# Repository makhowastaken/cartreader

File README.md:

# cartreader (name pending)

Apologies in advance, this repo is really all over the place. I'm trying to organize and document as I go and it's honestly taken more work to clean this project up and organize it than it has to actually create it in the first place. Things *will* be renamed eventually. 

This device was created from the schematic of [sanni's cart reader](https://github.com/sanni/cartreader) and even uses the same, unmodified firmware. Please see that repo for firmware and firmware updates. This device consists of two parts, the control unit which features the arduino itself, the peripherals, and the power supply, and then the interface adapter, which is largely just a passive adapter to allow you to insert whatever cart. Currently, feature parity has not been reached as I have yet to implement a N64 or Megadrive/Genesis adapter. 

## control unit ("sanni_pro")

The Brians of the device. This uses the aftermarket ATMEGA2560 "Pro" boards for a smaller footprint. The actual hardware is largely unchanged from the original Arduino Pros but the footprint is massively reduced. 

This part is designed to be "self contained" and will include all the hardware necessary to operate the device in a portable manner. You need one or more of the following adapters still. 

[Click here for more info, PCB files, and assembly instructions/information of the control unit.](PCB%20Files/control%20unit)

## gb/c and gba adapter ("sanni_gba")

This is the primary adapter that I made this whole module for. I really liked my original reader but I wanted something smaller. This module may actually be combined with any of the other modules by sandwiching the other module inbetween this board and the control unit module.  

[Click here for more info, PCB files, and assembly instructions/information of the GBA adapter.](PCB%20Files/adapters/sanni_gba_shield)

## 8 bit flash module adapter adapter ("sanni_flash")

This is equivalent to the module that plugs into the SNES/SFC slot on sanni's reader that allows you to directly interface with flash chips. It is working (finally) and should interface with the same modules as sanni's version. Only the TSOP48 adapter is tested and confirmed working. I don't have flash chips to test the other adapters. 

[Click here for more info, PCB files, and assembly instructions/information of the flash adapter.](PCB%20Files/adapters/sanni_flash_shield)

## snes / sfc adapter ("sanni_snes")

This adapter is a work in progress. I have uploaded the current version that I have tested and confirmed works (except for the untested CIC lock circuit but it should be fine). Confirmed dumping of SFC games and functionality with sanni's addon modules that interface with the SNES/SFC slot. 

[Click here for more info, PCB files, and assembly instructions/information of the SFC adapter.](PCB%20Files/adapters/sanni_snes_shield)

## n64 adapter

todo

## md/genesis adapter

todo

## other adapters

Sanni's NES/FC adapters, Wonderswan adapter, and SMS adapter should all work through the SNES/SFC adapter but are currently untested.

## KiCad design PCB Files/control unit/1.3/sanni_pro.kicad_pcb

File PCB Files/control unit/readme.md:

# control unit

Version 1.2c renders

BOM: 

|Part Desc|Link|Alternative Link|Cost (I used)|Notes|
:--|:--|:--|--:|:--|
|Arduino Mega 2560 Pro (EMBED, NOT MINI)|[https://www.aliexpress.com/item/MEGA-2560-PRO-Embed-CH340G-ATMEGA2560-16AU-Chip-With-Male-Pinheaders-Compatible-for-Arduino-Mega2560-Module/32968779271.html](https://www.aliexpress.com/item/MEGA-2560-PRO-Embed-CH340G-ATMEGA2560-16AU-Chip-With-Male-Pinheaders-Compatible-for-Arduino-Mega2560-Module/32968779271.html)|[https://www.aliexpress.com/item/Mega-2560-PRO-Embed-CH340G-ATmega2560-16AU-with-male-pinheaders-Compatible-for-Arduino-Mega-2560/32801785024.html](https://www.aliexpress.com/item/Mega-2560-PRO-Embed-CH340G-ATmega2560-16AU-with-male-pinheaders-Compatible-for-Arduino-Mega-2560/32801785024.html)|$8.60|I’d recommend the RobotDyn version. I’ve purchased four of these modules so far and two RobotDyn units were fine, one off-brand unit was fine while the other was DOA.|
|2x10K 0805 SMT Resistors|https://www.aliexpress.com/item/100Pcs-0805-SMD-1-4W-0R-10M-chip-resistor-0-10R-100R-220R-330R-470R-1K/32858225842.html| |$0.59|Might as well keep these things handy, they are useful for a lot of DIY type things. The board supports through-hole type resistors as well but I’d recommend the surface-mount ones anyway.|
|2x 4.3mm SMT SPST Push Button (OR mech keyboard switch)|https://novelkeys.xyz/collections/switches/products/novelkeys-x-kailh-low-profile-choc-thick-clicks|[https://www.aliexpress.com/item/2024658734.html](https://www.aliexpress.com/item/2024658734.html)|$2.55|I opted for mech keys that I already had on hand. The board supports Cherry MX (or equivalent), Alps (or equivalent), or Kailh Choc. You can also use 6x6 buttons but you’ll have to fold the legs under the button and solder from the side. Additionally, if you use standard tact switches, you want to make sure that the buttons you use stick out a few MM since it’s a bit of a pain in the rear to use them otherwise.|
|2x THT SPDT Slide Switch|https://www.aliexpress.com/item/50PCS-YT1998Y-SK12D07-Toggle-Switch-3Pin-PCB-2-Position-1P2T-SPDT-Miniature-Slide-Switch-Side-Knob/32827322833.html| |$1.75|You only need two of the 50, but I can’t find any smaller quantities for less. If you’ve already built one of Sanni’s cart reader shields, you probably already have these.|
|RGB LED (Common Anode)|[https://www.aliexpress.com/item/20Pcs-Multicolor-4pin-5mm-RGB-Led-Diode-Light-Lamp-Tricolor-Round-Common-Anode-LED-F5-Light/32852334348.html](https://www.aliexpress.com/item/20Pcs-Multicolor-4pin-5mm-RGB-Led-Diode-Light-Lamp-Tricolor-Round-Common-Anode-LED-F5-Light/32852334348.html)|https://www.ebay.com/itm/291548934125|$0.88|You only need one of the 50. Enjoy finding uses for the other 49. You can also omit this entirely.|
|OLED Screen|[https://www.aliexpress.com/item/0-96-inch-IIC-Serial-White-OLED-Display-Module-128X64-I2C-SSD1306-12864-LCD-Screen-Board/32896971385.html](https://www.aliexpress.com/item/0-96-inch-IIC-Serial-White-OLED-Display-Module-128X64-I2C-SSD1306-12864-LCD-Screen-Board/32896971385.html)| |$2.25|Comes in blue or white. Take your pick. I like the white.|
|TP4056 Charge Module with Low Voltage Protection|https://www.aliexpress.com/item/Free-Shipping-5V-1A-Micro-USB-18650-Lithium-Battery-Charging-Board-Charger-Module-Protection-Dual/32453058256.html| |$0.85|Micro USB variant is cheaper but this is your charge port and you can use Mini USB or USB C if you like. As long as you get the protected version, the footprint should match.|
|702540 Cell|[https://www.aliexpress.com/item/32878325857.html](https://www.aliexpress.com/item/32878325857.html)| |$8.00|Any “Game Boy Micro” sized battery should fit perfectly within the space between the actual cart interface shield and the arduino. If you have something laying around, that’s even better as this is the second most expensive part of the build (well, third depending on the PCBs)|
|5v 0.45A Voltage Regulator|[https://www.aliexpress.com/item/32786144773.html](https://www.aliexpress.com/item/32786144773.html)| |$1.54|A regulator that can handle more current would be better but this one is well within spec for Game Boy Games. SNES will require supplementary hardware. Any other three pin regulator should work, just mind that the PCB is expecting the middle pin to be ground.|
|3.3v 0.59A Voltage Regulator|[https://www.aliexpress.com/item/32914681832.html](https://www.aliexpress.com/item/32914681832.html)| |$1.47|Any three pin regulator should work, just mind that the middle pin is ground|
|Micro SD Module|[https://www.aliexpress.com/item/1PCS-Micro-SD-Storage-Expansion-Board-Mciro-SD-TF-Card-Memory-Shield-Module-SPI-For-Arduino/32523546123.html](https://www.aliexpress.com/item/1PCS-Micro-SD-Storage-Expansion-Board-Mciro-SD-TF-Card-Memory-Shield-Module-SPI-For-Arduino/32523546123.html)| |$1.04|This hardware does not support the full size SD Module (but only because I did not include the pins -- electrically, it should work fine).|
|Battery gauge (volt meter panel)|[https://www.aliexpress.com/item/32851937196.html](https://www.aliexpress.com/item/32851937196.html)| |$0.85|This is completely optional, but I like it. I also designed the PCB with this in mind so there will be an empty spot if you omit it.|
||||||
|2.54 MM Headers||||You only need the sockets if you think you might want to take this apart at some point. The sockets are required if you want to do more than rip whatever shield you assemble this with. XL pins are recommended for socket-less builds (not tested or linked).|
| Pins|https://www.aliexpress.com/item/10PCS-40Pin-1x40P-Male-Breakable-Pin-Header-Strip-2-54mm-Long-Blue-Red-White-Green-Yellow/32863408765.html| |$0.55|I had a ton of these laying around. With the pins, you can just break off however many you need and solder those on. You can also double-stack them pretty easily for things like the Arduino. The Arduino probably already came with pins though.|
| Sockets|[https://www.aliexpress.com/item/32889916876.html](https://www.aliexpress.com/item/32889916876.html)| |$4.32|You’ll need to get the 2x3, 2x16, and 2x20 option to socket the Arduino. I do not recommend socketing any other components on this model.|
|Total|||$36.79|Prices may have changed on somethings or shipping may be more or less expensive to your area.|

Please let me know if any parts go out of stock or if the listing disappears so that I can add an alternative. 

Assembly must be completed in order. Due to the close proximity of the parts, flush cutters are required and kapton tape for insulation is *highly* recommended. [Please see my video for an example of assembly.](https://youtu.be/GbIMFZ5j5U0)

---

New v1.3???

I have updated the PCB to use [my soft latching power button circuit](https://github.com/makhowastaken/Soft-Latching-Power-Button) and have otherwise slightly tweaked the traces to look better using oshpark's after dark fab process. Like previous boards, this is functionally identical and the only new feature is a momentary push button (swap one of the SPDT switches for the BOM listed in the above linked repo). Going forward, this is likely the board I will be updating but since I have not changed any critical dimensions, not much should change. 

This revision should work since all I did was combine two tested, working designs but since I have yet to actually assemble one, it should be considered untested.

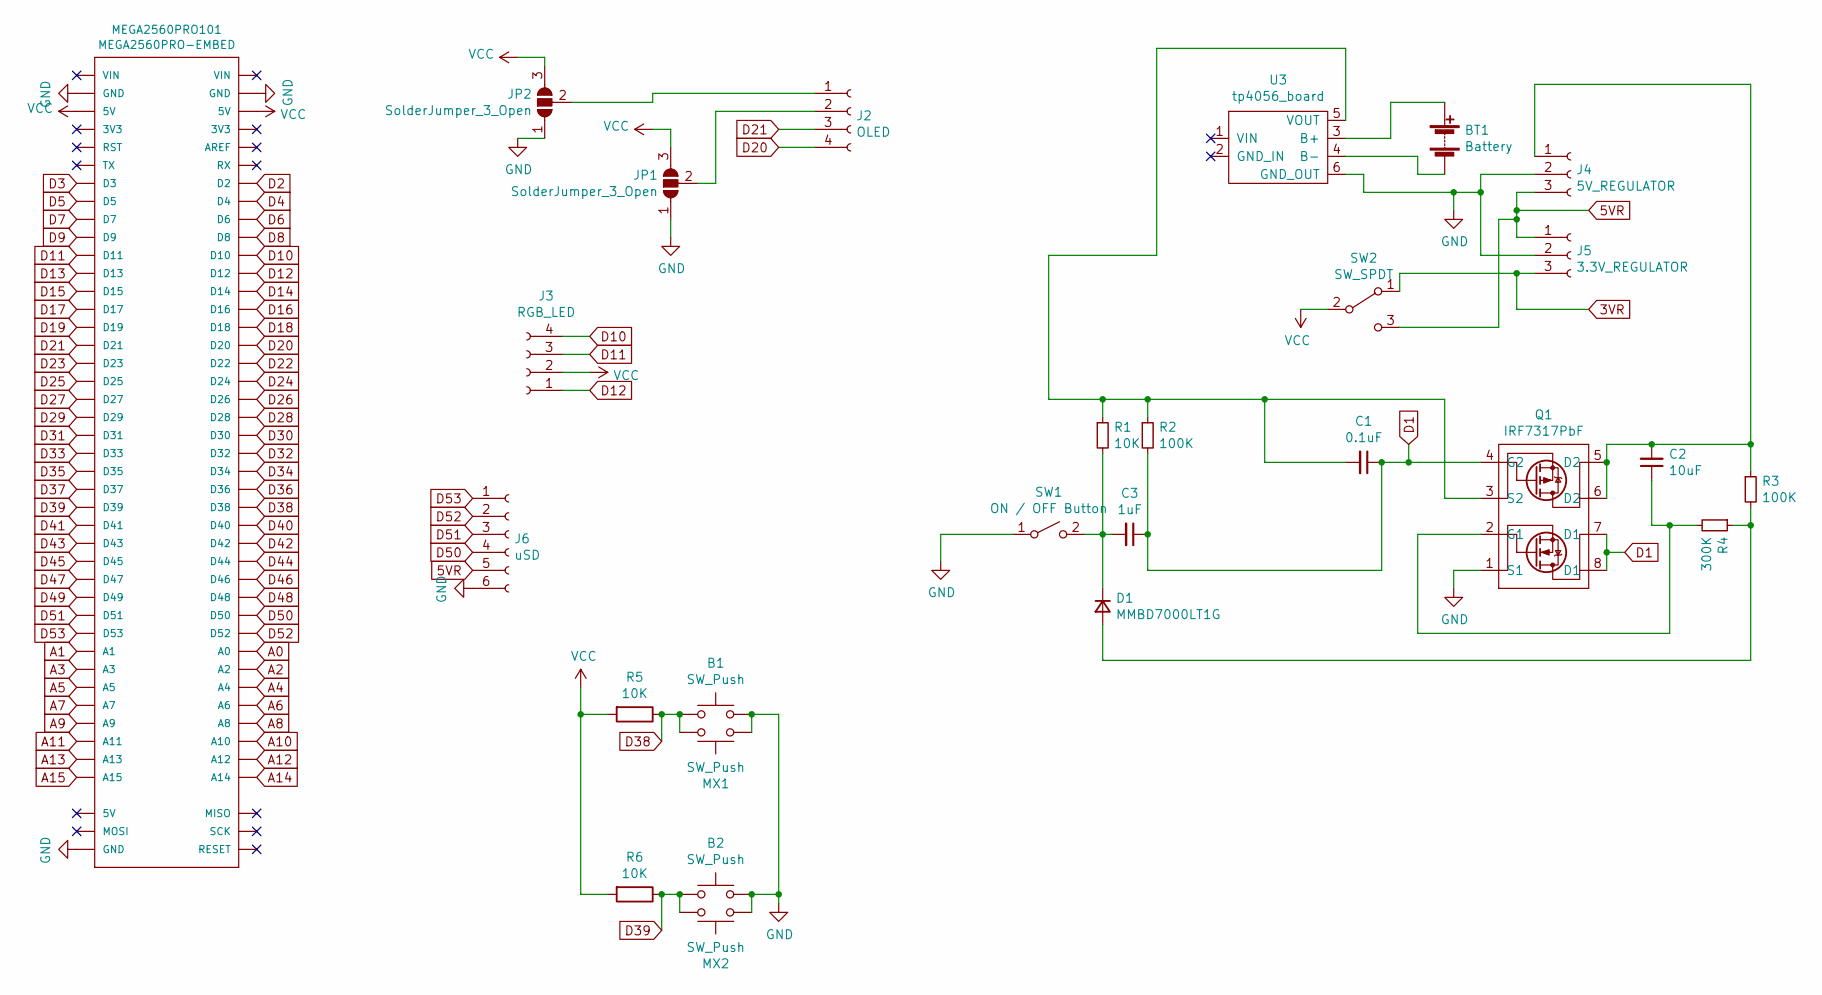
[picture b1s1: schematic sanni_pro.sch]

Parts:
B1, B2: SW_Push; SW_SPST_TL3342
BT1: Battery; PinHeader_1x02_P2.54mm_Vertical
C1: 0.1uF; C_0603_1608Metric_Pad1.05x0.95mm_HandSolder
C2: 10uF; C_0603_1608Metric_Pad1.05x0.95mm_HandSolder
C3: 1uF; C_0603_1608Metric_Pad1.05x0.95mm_HandSolder
D1: MMBD7000LT1G; D_SOT-23_ANK
J2: OLED; OLED_Module
J3: RGB_LED; PinSocket_1x04_P2.54mm_Vertical
J4: 5V_REGULATOR; PinSocket_1x03_P2.54mm_Vertical
J5: 3.3V_REGULATOR; PinSocket_1x03_P2.54mm_Vertical
J6: uSD; Catalex_uSD_BSilk
JP1, JP2: SolderJumper_3_Open; SolderJumper-3_P1.3mm_Open_RoundedPad1.0x1.5mm
MEGA2560PRO101: MEGA2560PRO-EMBED
MX1, MX2: SW_Push; MX-Alps-Choc-1U-NoLED_fixed
Q1: IRF7317PbF; SOIC-8_3.9x4.9mm_P1.27mm
R1: 10K; R_0603_1608Metric_Pad1.05x0.95mm_HandSolder
R2, R3: 100K; R_0603_1608Metric_Pad1.05x0.95mm_HandSolder
R4: 300K; R_0603_1608Metric_Pad1.05x0.95mm_HandSolder
R5, R6: 10K; Resistor-hybrid-3pad
SW1: ON / OFF Button; SW_SPST_TL3342
SW2: SW_SPDT; SW_CuK_OS102011MA1QN1_SPDT_Angled
U3: tp4056_board; 4056E_LiIon_loader_SMT

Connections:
3VR: J5.3, SW2.1 (A)
5VR: J4.3, J5.1, J6.5, SW2.3 (C)
A0: MEGA2560PRO101.A0
A1: MEGA2560PRO101.A1
A2: MEGA2560PRO101.A2
A3: MEGA2560PRO101.A3
A4: MEGA2560PRO101.A4
A5: MEGA2560PRO101.A5
A6: MEGA2560PRO101.A6
A7: MEGA2560PRO101.A7
A8: MEGA2560PRO101.A8
A9: MEGA2560PRO101.A9
A10: MEGA2560PRO101.A10
A11: MEGA2560PRO101.A11
A12: MEGA2560PRO101.A12
A13: MEGA2560PRO101.A13
A14: MEGA2560PRO101.A14
A15: MEGA2560PRO101.A15
D1: C1.1, C3.1, Q1.4 (G2), Q1.7 (D1), Q1.8 (D1), R2.2
D2: MEGA2560PRO101.D2
D3: MEGA2560PRO101.D3
D4: MEGA2560PRO101.D4
D5: MEGA2560PRO101.D5
D6: MEGA2560PRO101.D6
D7: MEGA2560PRO101.D7
D8: MEGA2560PRO101.D8
D9: MEGA2560PRO101.D9
D10: J3.4, MEGA2560PRO101.D10
D11: J3.3, MEGA2560PRO101.D11
D12: J3.1, MEGA2560PRO101.D12
D13: MEGA2560PRO101.D13
D14: MEGA2560PRO101.D14
D15: MEGA2560PRO101.D15
D16: MEGA2560PRO101.D16
D17: MEGA2560PRO101.D17
D18: MEGA2560PRO101.D18
D19: MEGA2560PRO101.D19
D20: J2.4, MEGA2560PRO101.D20
D21: J2.3, MEGA2560PRO101.D21
D22: MEGA2560PRO101.D22
D23: MEGA2560PRO101.D23
D24: MEGA2560PRO101.D24
D25: MEGA2560PRO101.D25
D26: MEGA2560PRO101.D26
D27: MEGA2560PRO101.D27
D28: MEGA2560PRO101.D28
D29: MEGA2560PRO101.D29
D30: MEGA2560PRO101.D30
D31: MEGA2560PRO101.D31
D32: MEGA2560PRO101.D32
D33: MEGA2560PRO101.D33
D34: MEGA2560PRO101.D34
D35: MEGA2560PRO101.D35
D36: MEGA2560PRO101.D36
D37: MEGA2560PRO101.D37
D38: B1.1, MEGA2560PRO101.D38, MX1.2, R5.1
D39: B2.1, MEGA2560PRO101.D39, MX2.2, R6.1
D40: MEGA2560PRO101.D40
D41: MEGA2560PRO101.D41
D42: MEGA2560PRO101.D42
D43: MEGA2560PRO101.D43
D44: MEGA2560PRO101.D44
D45: MEGA2560PRO101.D45
D46: MEGA2560PRO101.D46
D47: MEGA2560PRO101.D47
D48: MEGA2560PRO101.D48
D49: MEGA2560PRO101.D49
D50: J6.4, MEGA2560PRO101.D50
D51: J6.3, MEGA2560PRO101.D51
D52: J6.2, MEGA2560PRO101.D52
D53: J6.1, MEGA2560PRO101.D53
GND: B1.2, B2.2, J4.2, J5.2, J6.6, JP1.1 (A), JP2.1 (A), MEGA2560PRO101.GND@1 (GND), MEGA2560PRO101.GND@2 (GND), MEGA2560PRO101.GND@3 (GND), MX1.1, MX2.1, Q1.1 (S1), SW1.1 (A), U3.6 (GND_OUT)
unnamed: BT1.1 (+), U3.3 (B+)
unnamed: BT1.2 (-), U3.4 (B-)
unnamed: C2.1, Q1.2 (G1), R4.2
unnamed: C3.2, D1.1 (K), R1.2, SW1.2 (B)
unnamed: D1.2 (A), R3.2, R4.1
unnamed: J2.1, JP2.2 (C)
unnamed: J2.2, JP1.2 (C)
VCC: J3.2, JP1.3 (B), JP2.3 (B), MEGA2560PRO101.5V@1 (5V), MEGA2560PRO101.5V@2 (5V), R5.2, R6.2, SW2.2 (B)

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
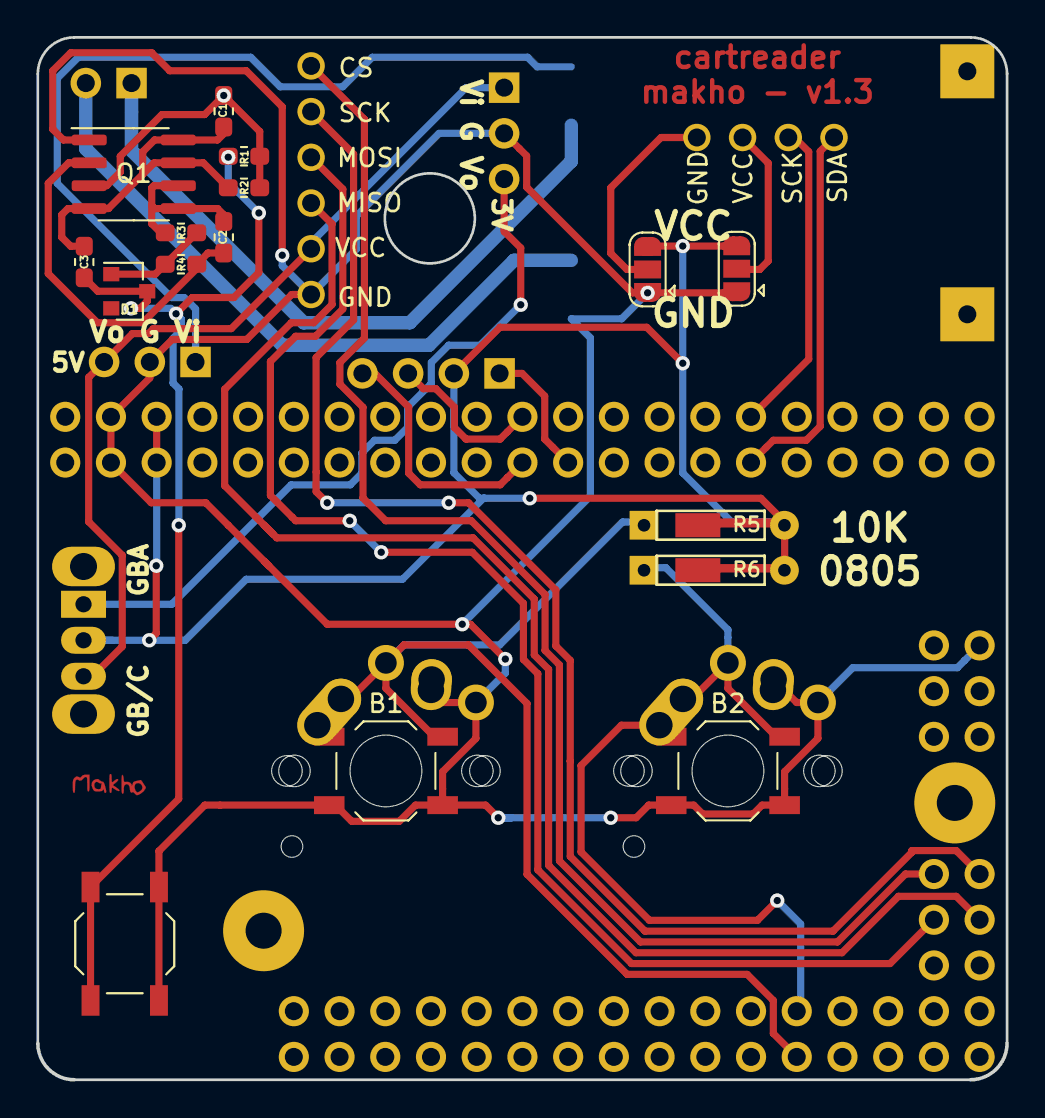
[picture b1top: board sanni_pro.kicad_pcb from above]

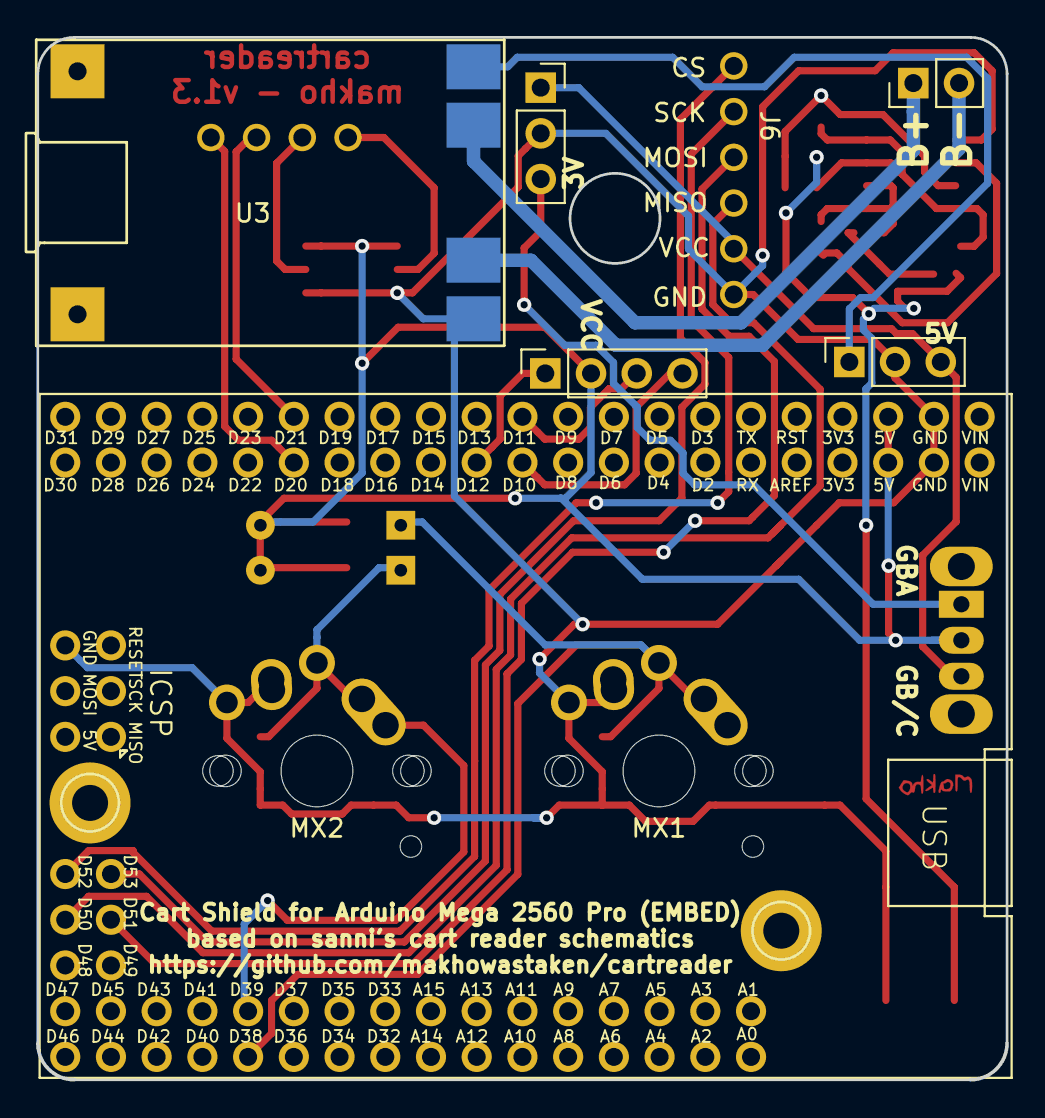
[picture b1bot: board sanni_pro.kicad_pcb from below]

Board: 2 copper layers, 53.8 x 57.9 mm, 28 parts (6 on the bottom side), 25 nets.

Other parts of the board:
Ref**: Val**; makho_micro_fmask

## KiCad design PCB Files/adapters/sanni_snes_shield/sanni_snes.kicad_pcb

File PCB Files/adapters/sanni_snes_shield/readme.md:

# snes / sfc adapter

Version 1.2c renders

this is a work in progress. This is currently tested and confirmed working but some things are in dumb spots. I kinda just winged this whole thing.

BOM:
(todo)
The cart slot, CIC lock hardware, clock signal generator, two more of the SPDT switches that you used for the control unit, and probably something else that I'm forgetting.

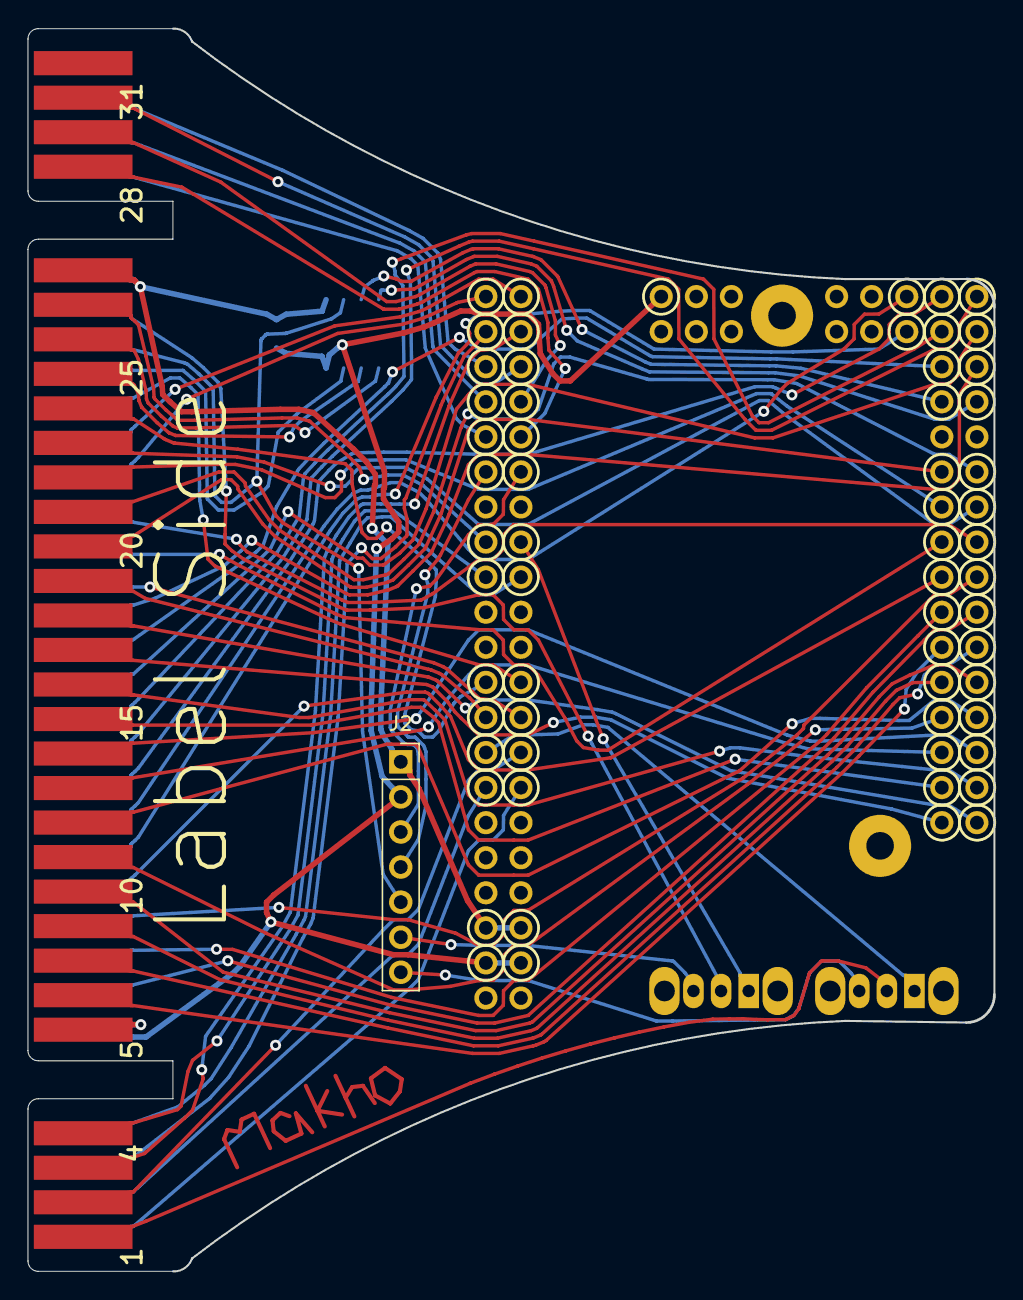
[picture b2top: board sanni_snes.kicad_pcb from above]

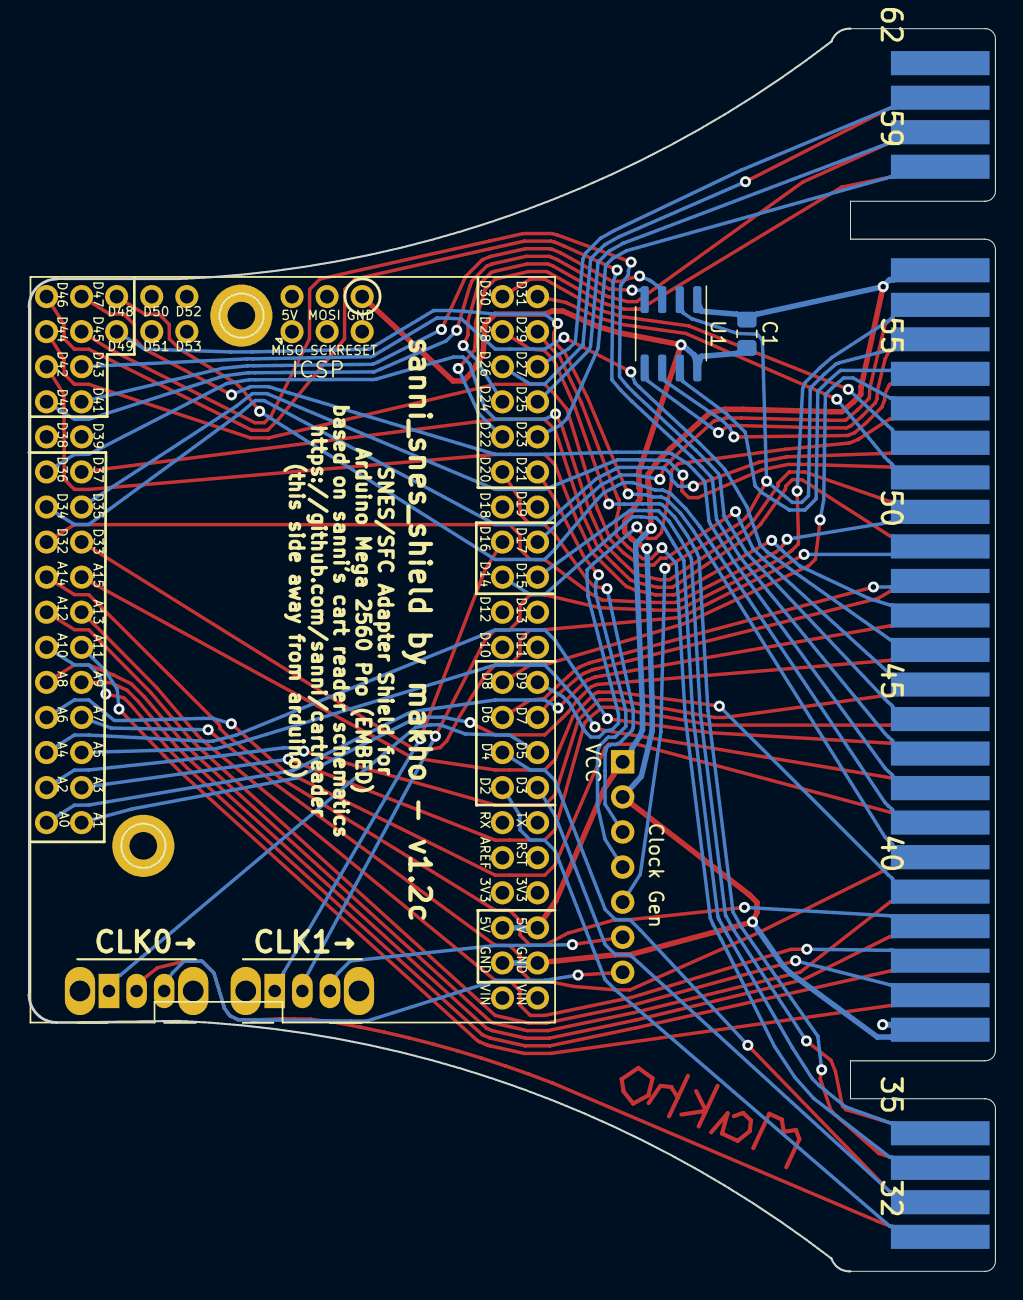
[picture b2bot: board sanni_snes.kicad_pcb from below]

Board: 2 copper layers, 69.9 x 90.0 mm, 7 parts (5 on the bottom side), 66 nets.

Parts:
C1: 100nF; C_0805_2012Metric_Pad1.15x1.40mm_HandSolder
J1: SNES_EXP_CONN; SNES-CART-EXP-EDGE-CONN
J2: CLOCKGEN; PinSocket_1x07_P2.54mm_Vertical
MEGA2560PRO101: MEGA2560PRO-EMBED
SW1: CLK0; SW_CuK_OS102011MA1QN1_SPDT_Angled
SW2: CLK1; SW_CuK_OS102011MA1QN1_SPDT_Angled
U1: PIC12F629-ISN; SOIC-8_3.9x4.9mm_P1.27mm

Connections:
A0: J1.17, MEGA2560PRO101.A0
A1: J1.16, MEGA2560PRO101.A1
A2: J1.15, MEGA2560PRO101.A2
A3: J1.14, MEGA2560PRO101.A3
A4: J1.13, MEGA2560PRO101.A4
A5: J1.12, MEGA2560PRO101.A5
A6: J1.11, MEGA2560PRO101.A6
A7: J1.10, MEGA2560PRO101.A7
A8: J1.9, MEGA2560PRO101.A8
A9: J1.8, MEGA2560PRO101.A9
A10: J1.7, MEGA2560PRO101.A10
A11: J1.6, MEGA2560PRO101.A11
A12: J1.37, MEGA2560PRO101.A12
A13: J1.38, MEGA2560PRO101.A13
A14: J1.39, MEGA2560PRO101.A14
A15: J1.40, MEGA2560PRO101.A15
CIC0: J1.55, U1.7
CIC1: J1.24, U1.6
CICCLK: J1.56, J2.5, U1.2
CLK0: J2.7, SW1.3
CLK1: J2.6, SW2.3
D2: J1.32, MEGA2560PRO101.D2
D3: J1.33, MEGA2560PRO101.D3
D4: J1.2, MEGA2560PRO101.D4
D5: MEGA2560PRO101.D5, SW1.1
D6: J1.49, MEGA2560PRO101.D6
D7: J1.18, MEGA2560PRO101.D7
D8: J1.54, MEGA2560PRO101.D8
D9: J1.23, MEGA2560PRO101.D9
D14: J1.35, MEGA2560PRO101.D14
D15: J1.4, MEGA2560PRO101.D15
D16: MEGA2560PRO101.D16, SW2.1
D17: J1.26, MEGA2560PRO101.D17
D20: J2.3, MEGA2560PRO101.D20
D21: J2.4, MEGA2560PRO101.D21
D22: J1.28, MEGA2560PRO101.D22
D23: J1.59, MEGA2560PRO101.D23
D24: J1.29, MEGA2560PRO101.D24
D25: J1.60, MEGA2560PRO101.D25
D26: J1.30, MEGA2560PRO101.D26
D27: J1.61, MEGA2560PRO101.D27
D28: J1.3, MEGA2560PRO101.D28
D29: J1.34, MEGA2560PRO101.D29
D30: J1.53, MEGA2560PRO101.D30
D31: J1.52, MEGA2560PRO101.D31
D32: J1.51, MEGA2560PRO101.D32
D33: J1.50, MEGA2560PRO101.D33
D34: J1.22, MEGA2560PRO101.D34
D35: J1.21, MEGA2560PRO101.D35
D36: J1.20, MEGA2560PRO101.D36
D37: J1.19, MEGA2560PRO101.D37
D40: MEGA2560PRO101.D40, U1.4
D41: MEGA2560PRO101.D41, U1.3
D42: J1.48, MEGA2560PRO101.D42
D43: J1.47, MEGA2560PRO101.D43
D44: J1.46, MEGA2560PRO101.D44
D45: J1.45, MEGA2560PRO101.D45
D46: J1.44, MEGA2560PRO101.D46
D47: J1.43, MEGA2560PRO101.D47
D48: J1.42, MEGA2560PRO101.D48
D49: J1.41, MEGA2560PRO101.D49
GND: C1.2, J1.5, J1.36, J2.2, MEGA2560PRO101.GND@1, MEGA2560PRO101.GND@2, MEGA2560PRO101.GND@3, U1.8
Reset_In: J1.25, U1.5
SW1CLK: J1.1, SW1.2
SW2CLK: J1.57, SW2.2
VCC: C1.1, J1.27, J1.58, J2.1, MEGA2560PRO101.5V@1, MEGA2560PRO101.5V@2, U1.1

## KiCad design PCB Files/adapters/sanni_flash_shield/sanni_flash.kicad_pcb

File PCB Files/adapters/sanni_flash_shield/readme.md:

# 8 bit flash adapter

Version 1.2c renders

BOM:
(todo)
lots of pin headers, two more SPDT switches that you used to build the control unit (only required for the SOP adapter), and then the adapters themselves. 

[assembly video here (soon)](https://youtu.be/Xz5Vwh5hB-U)

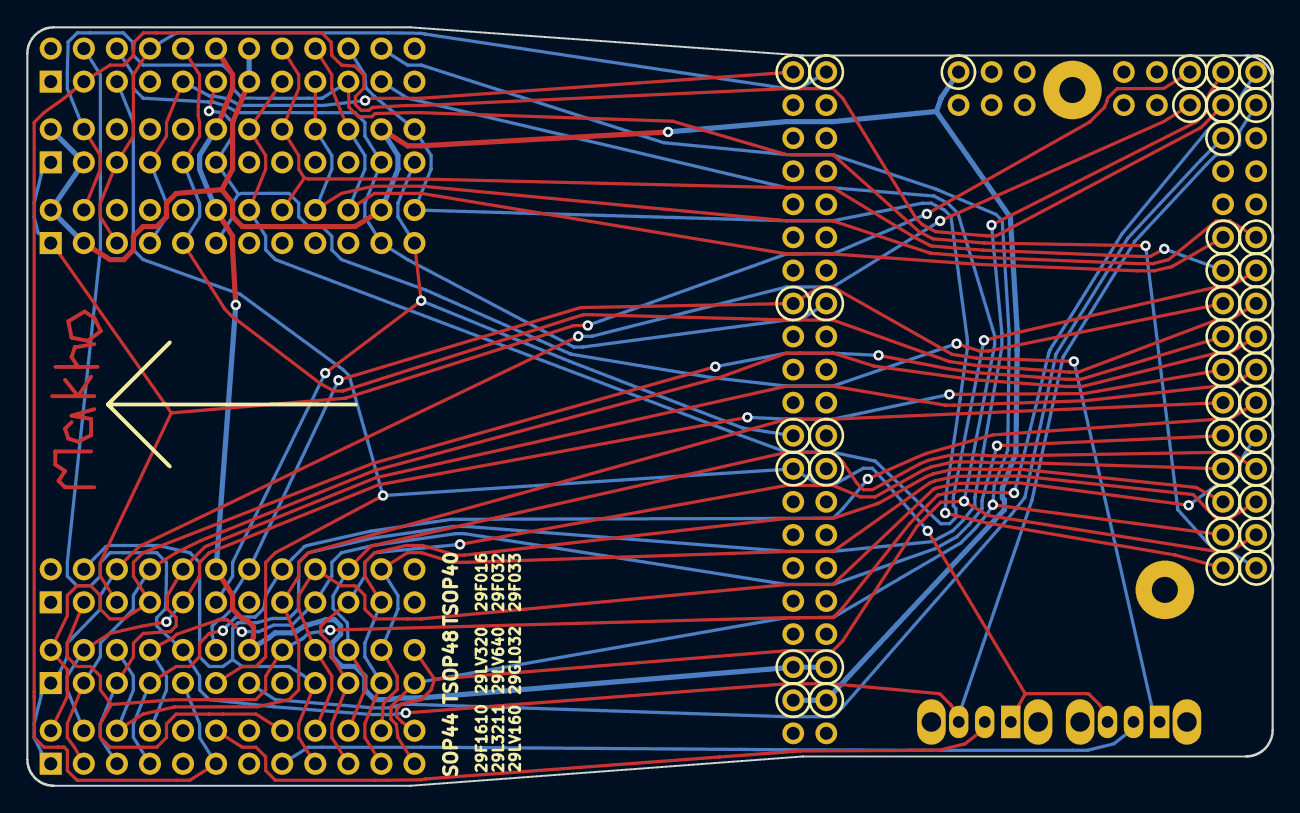
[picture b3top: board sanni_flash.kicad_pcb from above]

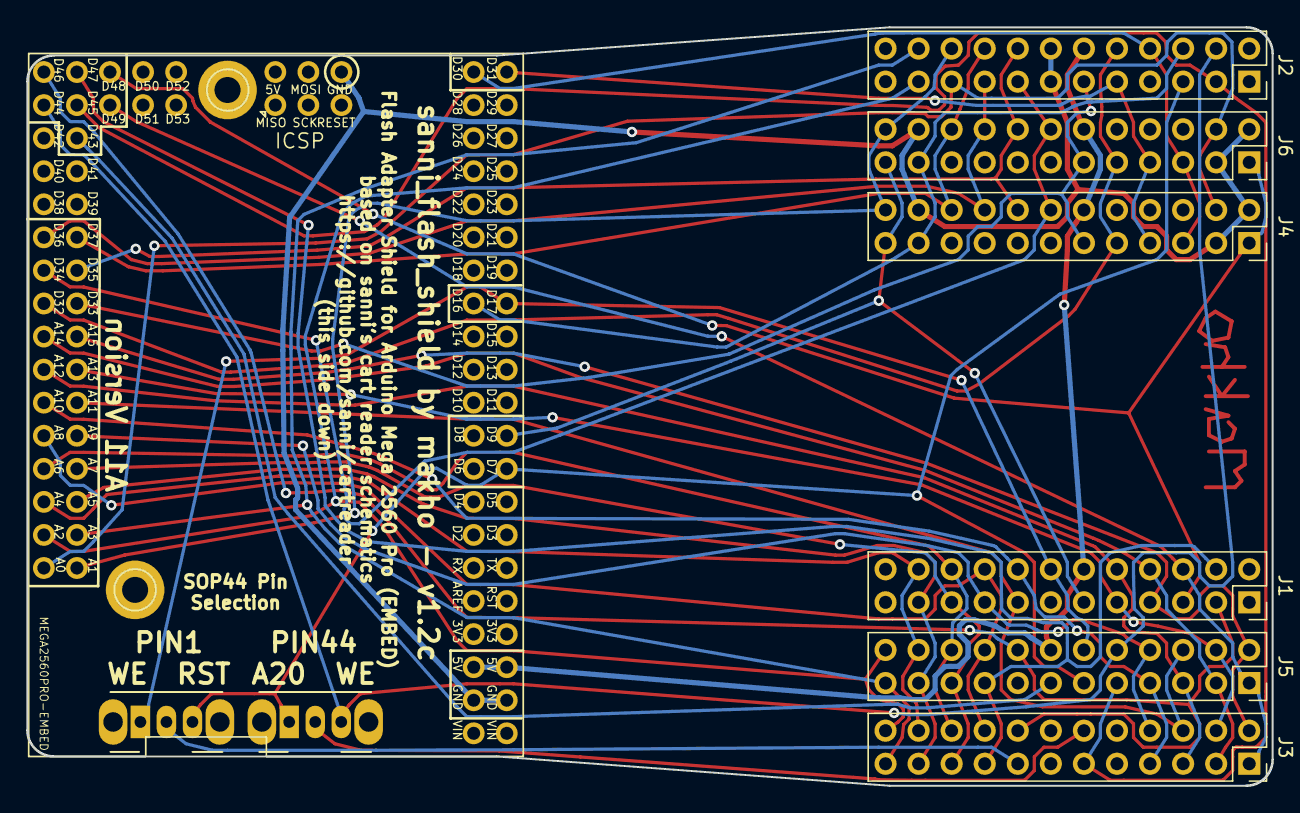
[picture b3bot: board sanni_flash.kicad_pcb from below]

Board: 2 copper layers, 95.7 x 58.3 mm, 9 parts (9 on the bottom side), 39 nets.

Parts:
J1: TSOP40_L; PinSocket_2x12_P2.54mm_Vertical
J2: TSOP40_R; PinSocket_2x12_P2.54mm_Vertical
J3: SOP44_L; PinSocket_2x12_P2.54mm_Vertical
J4: SOP44_R; PinSocket_2x12_P2.54mm_Vertical
J5: TSOP48_L; PinSocket_2x12_P2.54mm_Vertical
J6: TSOP48_R; PinSocket_2x12_P2.54mm_Vertical
MEGA2560PRO101: MEGA2560PRO-EMBED
SW1: A20/WE (SOP44); SW_CuK_OS102011MA1QN1_SPDT_Angled
SW2: WE/RST (SOP44); SW_CuK_OS102011MA1QN1_SPDT_Angled

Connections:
A0: J2.19, J4.4, J6.4, MEGA2560PRO101.A0
A1: J2.20, J4.24, J6.24, MEGA2560PRO101.A1
A2: J2.21, J3.24, J5.24, MEGA2560PRO101.A2
A3: J2.22, J3.23, J5.23, MEGA2560PRO101.A3
A4: J1.22, J3.22, J5.22, MEGA2560PRO101.A4
A5: J1.21, J3.21, J5.21, MEGA2560PRO101.A5
A6: J1.20, J3.20, J5.20, MEGA2560PRO101.A6
A7: J1.19, J3.19, J5.19, MEGA2560PRO101.A7
A8: J1.18, J3.18, J5.18, MEGA2560PRO101.A8
A9: J1.17, J3.8, J5.8, MEGA2560PRO101.A9
A10: J1.16, J3.7, J5.7, MEGA2560PRO101.A10
A11: J1.15, J3.6, J5.6, MEGA2560PRO101.A11
A12: J1.10, J3.5, J5.5, MEGA2560PRO101.A12
A13: J1.9, J3.4, J5.4, MEGA2560PRO101.A13
A14: J1.8, J3.3, J5.3, MEGA2560PRO101.A14
A15: J1.7, J3.2, J5.2, MEGA2560PRO101.A15
A20WE: J3.12, SW1.2
D7: J2.5, J5.11, MEGA2560PRO101.D7, SW1.1, SW2.3
D9: J1.11, J4.23, J6.23, MEGA2560PRO101.D9
D16: J2.6, J4.21, J6.21, MEGA2560PRO101.D16
D17: J1.14, J5.12, MEGA2560PRO101.D17, SW2.1
D30: J2.8, J4.5, J6.5, MEGA2560PRO101.D30
D31: J2.9, J4.7, J6.7, MEGA2560PRO101.D31
D32: J2.10, J4.9, J6.9, MEGA2560PRO101.D32
D33: J2.11, J4.11, J6.11, MEGA2560PRO101.D33
D34: J2.15, J4.14, J6.14, MEGA2560PRO101.D34
D35: J2.16, J4.16, J6.16, MEGA2560PRO101.D35
D36: J2.17, J4.18, J6.18, MEGA2560PRO101.D36
D37: J2.18, J4.20, J6.20, MEGA2560PRO101.D37
D43: J5.13, MEGA2560PRO101.D43
D44: J2.4, J5.10, MEGA2560PRO101.D44, SW1.3
D45: J2.3, J3.11, J5.9, MEGA2560PRO101.D45
D46: J1.3, J3.16, J5.16, MEGA2560PRO101.D46
D47: J1.4, J3.17, J5.17, MEGA2560PRO101.D47
D48: J1.5, J4.1, J6.1, MEGA2560PRO101.D48
D49: J1.6, J3.1, J5.1, MEGA2560PRO101.D49
GND: J2.13, J2.14, J4.2, J4.3, J4.22, J6.2, J6.3, J6.22, MEGA2560PRO101.GND@1, MEGA2560PRO101.GND@2, MEGA2560PRO101.GND@3
VCC: J1.12, J2.12, J4.12, J5.14, J6.12, MEGA2560PRO101.5V@1, MEGA2560PRO101.5V@2
WERST: J3.15, SW2.2

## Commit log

2020-03-11 Rename flash.md to readme.md
2020-03-11 Rename controlunit.md to readme.md
2020-04-23 Update readme.md
    fixed broken switch link
2020-09-10 fixed folder name
2020-09-10 made folder organization more consistent
